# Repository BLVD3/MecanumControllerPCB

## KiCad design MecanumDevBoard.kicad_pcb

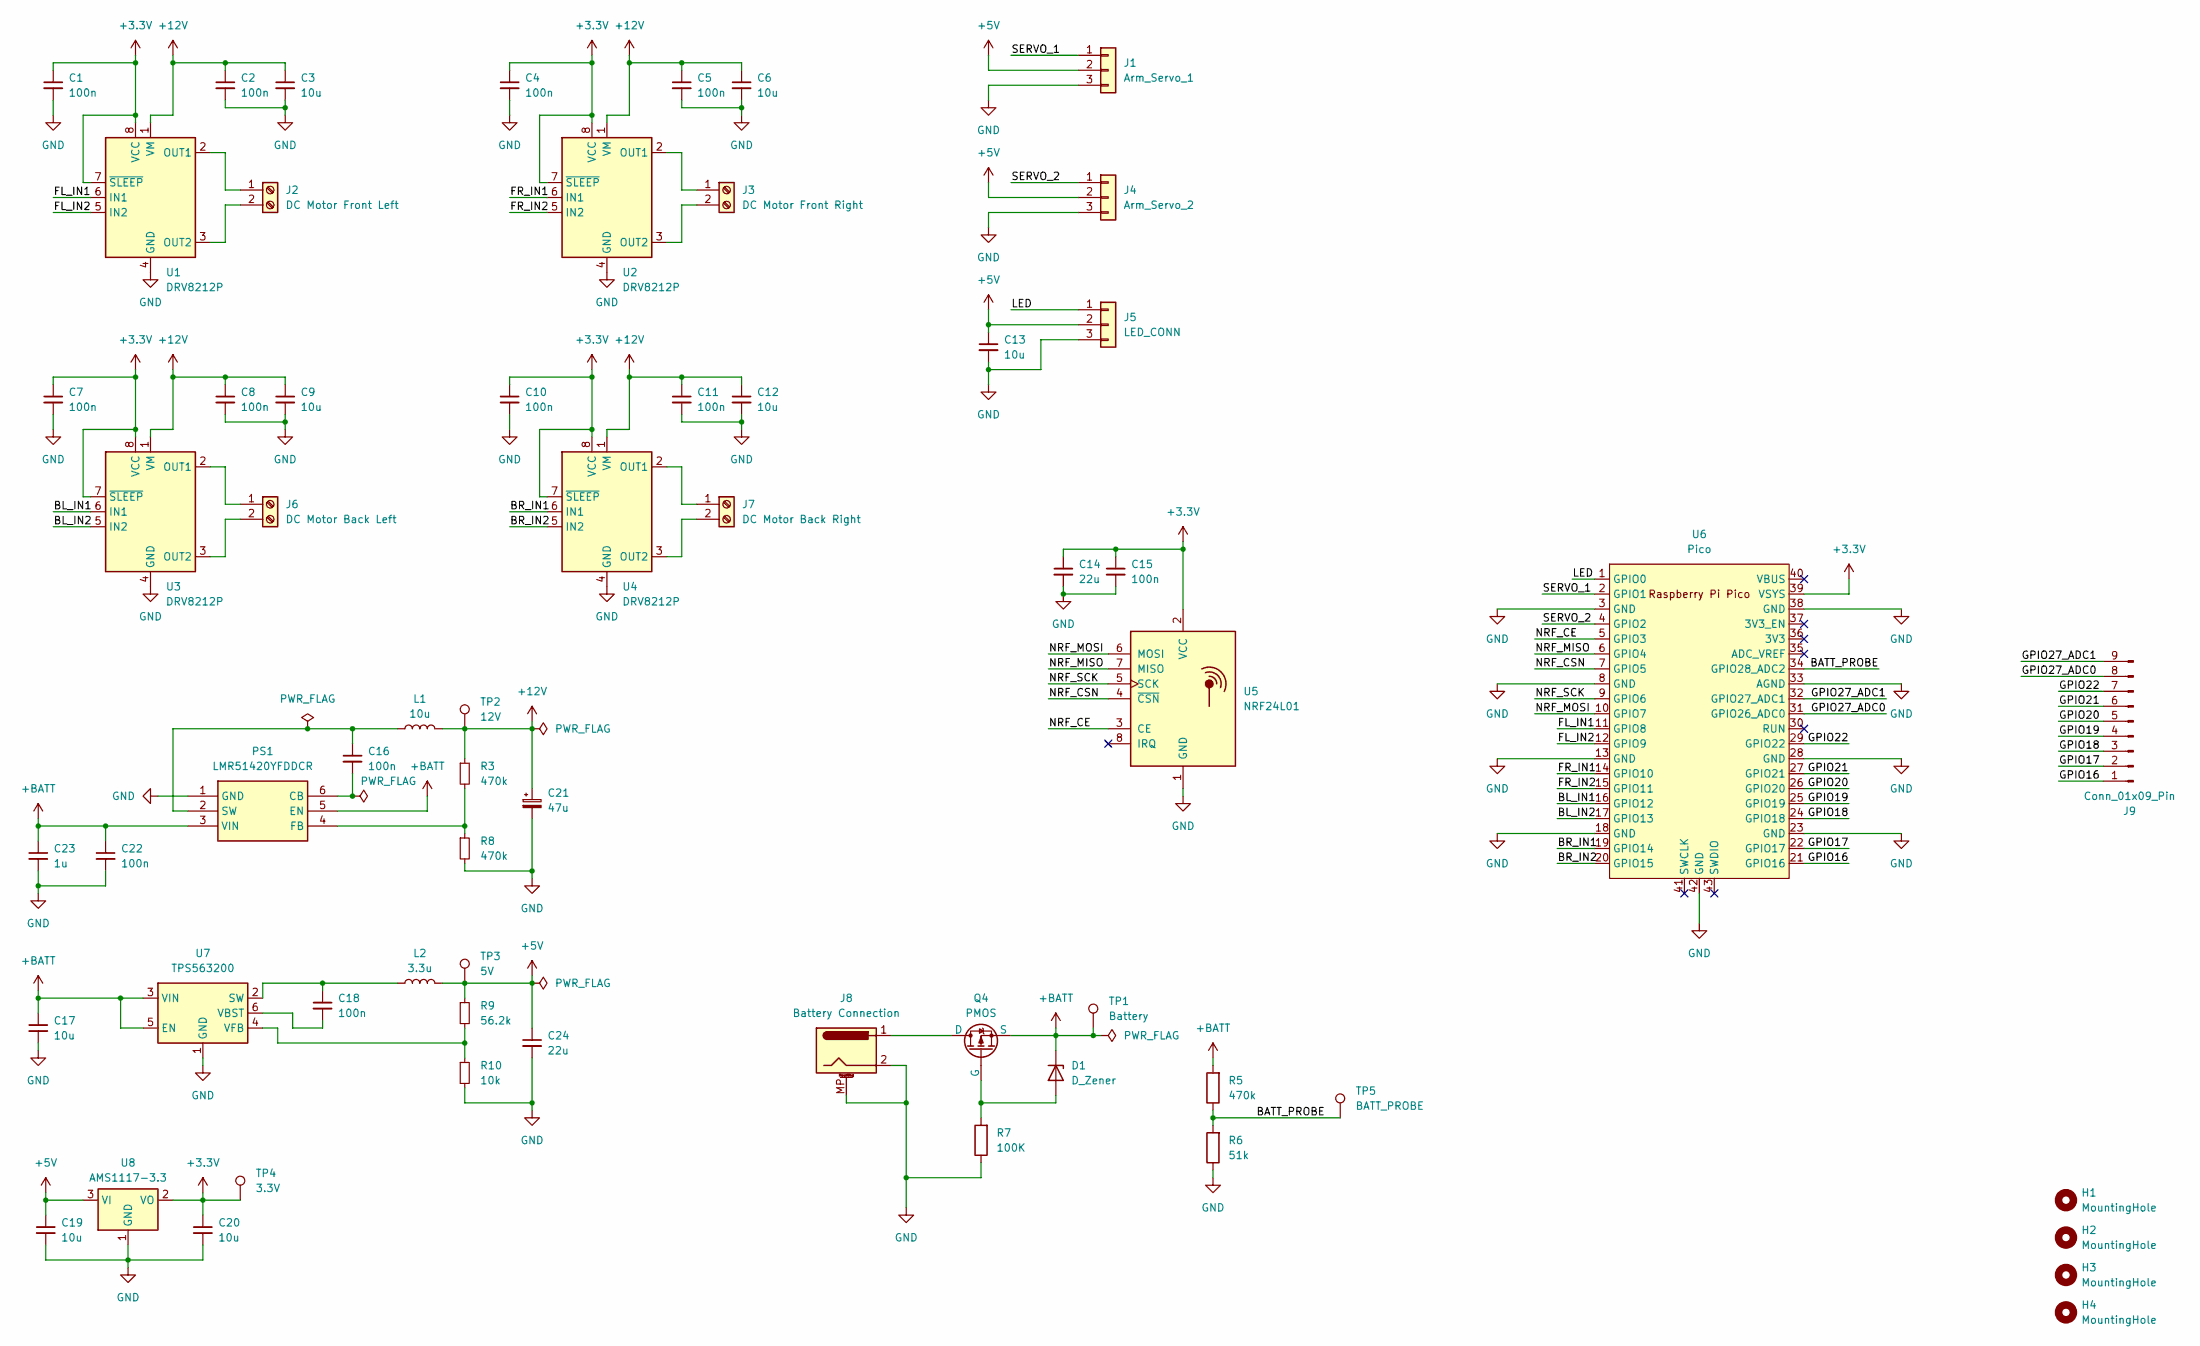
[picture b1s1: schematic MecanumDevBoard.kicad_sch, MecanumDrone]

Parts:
C1, C2, C4, C5, C7, C8, C10, C11, C15, C16, C18, C22: 100n; C_0603_1608Metric
C3, C6, C9, C12, C13, C17, C19, C20: 10u; C_0805_2012Metric
C14, C24: 22u; C_0805_2012Metric
C21: 47u; CP_Radial_D8.0mm_P5.00mm
C23: 1u; C_0603_1608Metric
D1: D_Zener; D_SOD-123
H1, H2, H3, H4: MountingHole; MountingHole_2.2mm_M2
J1: Arm_Servo_1; PinHeader_1x03_P2.54mm_Vertical
J2: DC Motor Front Left; TerminalBlock_Phoenix_MPT-0,5-2-2.54_1x02_P2.54mm_Horizontal
J3: DC Motor Front Right; TerminalBlock_Phoenix_MPT-0,5-2-2.54_1x02_P2.54mm_Horizontal
J4: Arm_Servo_2; PinHeader_1x03_P2.54mm_Vertical
J5: LED_CONN; PinHeader_1x03_P2.54mm_Vertical
J6: DC Motor Back Left; TerminalBlock_Phoenix_MPT-0,5-2-2.54_1x02_P2.54mm_Horizontal
J7: DC Motor Back Right; TerminalBlock_Phoenix_MPT-0,5-2-2.54_1x02_P2.54mm_Horizontal
J8: Battery Connection; BarrelJack_Horizontal
J9: Conn_01x09_Pin; PinHeader_1x09_P2.54mm_Vertical
L1: 10u; L_Bourns-SRN6028
L2: 3.3u; L_Bourns-SRN6028
PS1: LMR51420YFDDCR; SOT95P280X110-6N; Manufacturer_Part_Number LMR51420YFDDCR; Mouser Part Number 595-LMR51420YFDDCR
Q4: PMOS; SOT-23
R3, R5, R8: 470k; R_0805_2012Metric
R6: 51k; R_0603_1608Metric
R7: 100K; R_0805_2012Metric
R9: 56.2k; R_0603_1608Metric
R10: 10k; R_0805_2012Metric
TP1: Battery; TestPoint_Pad_D1.0mm
TP2: 12V; TestPoint_Pad_D1.0mm
TP3: 5V; TestPoint_Pad_D1.0mm
TP4: 3.3V; TestPoint_Pad_D1.0mm
TP5: BATT_PROBE; TestPoint_Pad_D1.0mm
U1, U2, U3, U4: DRV8212P; WSON-8-1EP_2x2mm_P0.5mm_EP0.9x1.6mm
U5: NRF24L01; nRF24L01_Breakout
U6: Pico; RPi_Pico_SMD_TH
U7: TPS563200; SOT-23-6
U8: AMS1117-3.3; SOT-223-3_TabPin2

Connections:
+3.3V: C1.1, C4.1, C7.1, C10.1, C14.1, C15.1, C20.1, TP4.1, U1.7 (~SLEEP), U1.8 (VCC), U2.7 (~SLEEP), U2.8 (VCC), U3.7 (~SLEEP), U3.8 (VCC), U4.7 (~SLEEP), U4.8 (VCC), U5.2 (VCC), U6.39 (VSYS), U8.2 (VO)
+5V: C13.1, C19.1, C24.1, J1.2, J4.2, J5.2, L2.2, R9.1, TP3.1, U8.3 (VI)
+12V: C2.1, C3.1, C5.1, C6.1, C8.1, C9.1, C11.1, C12.1, C21.1, L1.2, R3.1, TP2.1, U1.1 (VM), U2.1 (VM), U3.1 (VM), U4.1 (VM)
+BATT: C17.1, C22.1, C23.1, D1.1 (K), PS1.3 (VIN), PS1.5 (EN), Q4.3 (S), R5.2, TP1.1, U7.3 (VIN), U7.5 (EN)
/BATT_PROBE: R5.1, R6.2, TP5.1, U6.34 (GPIO28_ADC2)
/BL_IN1: U3.6 (IN1), U6.16 (GPIO12)
/BL_IN2: U3.5 (IN2), U6.17 (GPIO13)
/BR_IN1: U4.6 (IN1), U6.19 (GPIO14)
/BR_IN2: U4.5 (IN2), U6.20 (GPIO15)
/FL_IN1: U1.6 (IN1), U6.11 (GPIO8)
/FL_IN2: U1.5 (IN2), U6.12 (GPIO9)
/FR_IN1: U2.6 (IN1), U6.14 (GPIO10)
/FR_IN2: U2.5 (IN2), U6.15 (GPIO11)
/GPIO16: J9.1, U6.21 (GPIO16)
/GPIO17: J9.2, U6.22 (GPIO17)
/GPIO18: J9.3, U6.24 (GPIO18)
/GPIO19: J9.4, U6.25 (GPIO19)
/GPIO20: J9.5, U6.26 (GPIO20)
/GPIO21: J9.6, U6.27 (GPIO21)
/GPIO22: J9.7, U6.29 (GPIO22)
/GPIO27_ADC0: J9.8, U6.31 (GPIO26_ADC0)
/GPIO27_ADC1: J9.9, U6.32 (GPIO27_ADC1)
/LED: J5.1, U6.1 (GPIO0)
/NRF_CE: U5.3 (CE), U6.5 (GPIO3)
/NRF_CSN: U5.4 (~CSN), U6.7 (GPIO5)
/NRF_MISO: U5.7 (MISO), U6.6 (GPIO4)
/NRF_MOSI: U5.6 (MOSI), U6.10 (GPIO7)
/NRF_SCK: U5.5 (SCK), U6.9 (GPIO6)
/SERVO_1: J1.1, U6.2 (GPIO1)
/SERVO_2: J4.1, U6.4 (GPIO2)
GND: C1.2, C2.2, C3.2, C4.2, C5.2, C6.2, C7.2, C8.2, C9.2, C10.2, C11.2, C12.2, C13.2, C14.2, C15.2, C17.2, C19.2, C20.2, C21.2, C22.2, C23.2, C24.2, J1.3, J4.3, J5.3, J8.2, J8.MP (MountPin), PS1.1 (GND), R6.1, R7.1, R8.2, R10.2, U1.4 (GND), U1.9 (GND), U2.4 (GND), U2.9 (GND), U3.4 (GND), U3.9 (GND), U4.4 (GND), U4.9 (GND), U5.1 (GND), U6.3 (GND), U6.8 (GND), U6.13 (GND), U6.18 (GND), U6.23 (GND), U6.28 (GND), U6.33 (AGND), U6.38 (GND), U6.42 (GND), U7.1 (GND), U8.1 (GND)
unnamed: D1.2 (A), Q4.2 (G), R7.2
unnamed: J2.1, U1.2 (OUT1)
unnamed: J2.2, U1.3 (OUT2)
unnamed: J3.1, U2.2 (OUT1)
unnamed: J3.2, U2.3 (OUT2)
unnamed: J6.1, U3.2 (OUT1)
unnamed: J6.2, U3.3 (OUT2)
unnamed: J7.1, U4.2 (OUT1)
unnamed: J7.2, U4.3 (OUT2)
unnamed: C16.2, PS1.6 (CB)
unnamed: PS1.4 (FB), R3.2, R8.1
unnamed: C16.1, L1.1, PS1.2 (SW)
unnamed: J8.1, Q4.1 (D)
unnamed: C18.1, L2.1, U7.2 (SW)
unnamed: C18.2, U7.6 (VBST)
unnamed: R9.2, R10.1, U7.4 (VFB)

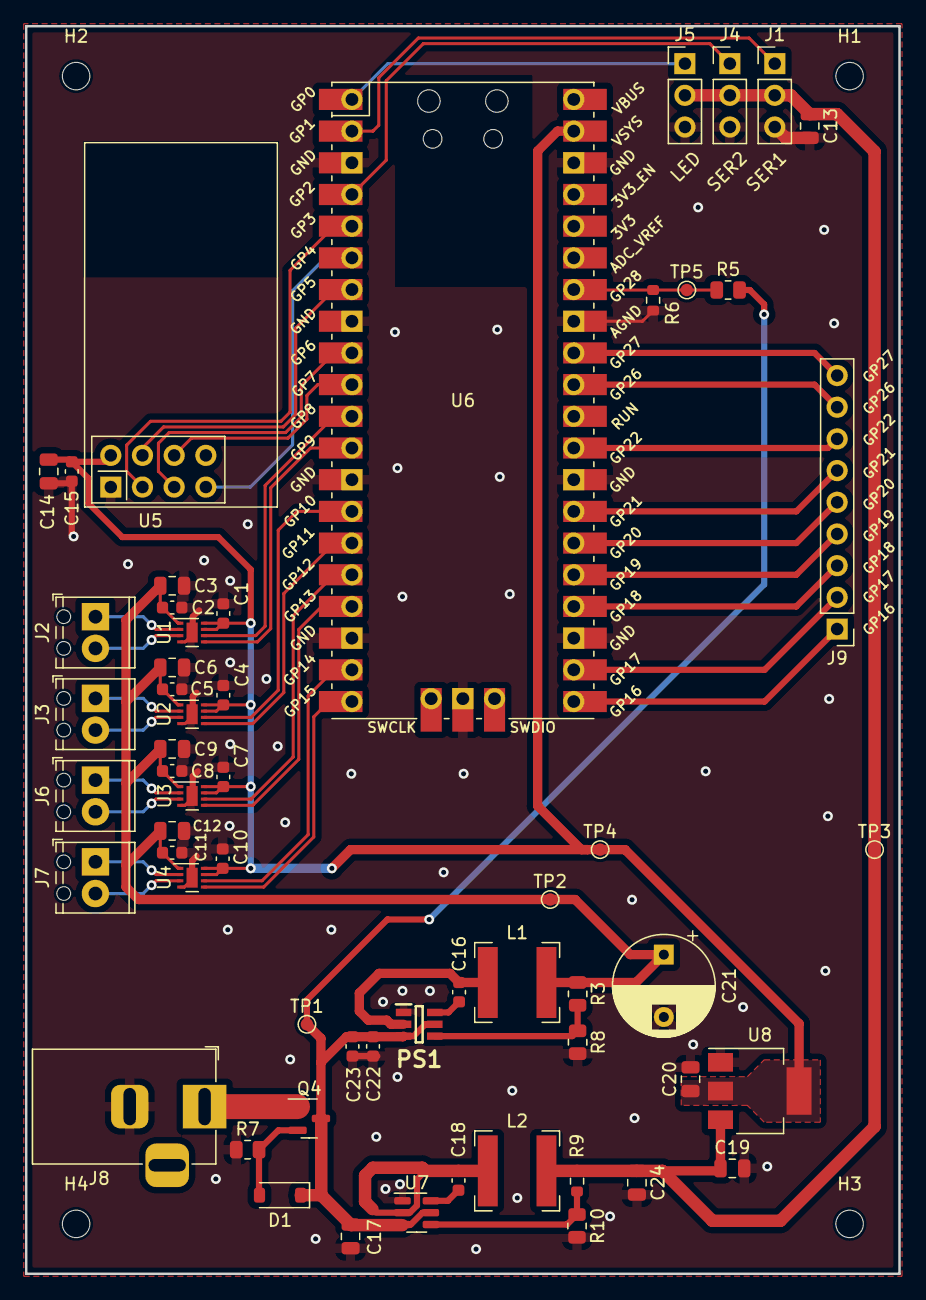
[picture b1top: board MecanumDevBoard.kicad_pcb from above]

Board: 2 copper layers, 70.0 x 100.0 mm, 62 parts (0 on the bottom side), 47 nets.

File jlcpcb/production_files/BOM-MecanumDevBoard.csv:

Comment,Designator,Footprint,LCSC
100n,"C1,C10,C11,C15,C16,C18,C2,C22,C4,C5,C7,C8",C_0603_1608Metric,C14663
100K,R7,R_0805_2012Metric,C149504
PMOS,Q4,SOT-23,C15127
1u,C23,C_0603_1608Metric,C15849
10u,"C12,C13,C17,C19,C20,C3,C6,C9",C_0805_2012Metric,C15850
10k,R10,R_0805_2012Metric,C17414
470k,"R3,R5,R8",R_0805_2012Metric,C17709
51k,R6,R_0603_1608Metric,C23196
56.2k,R9,R_0603_1608Metric,C23206
DRV8212P,"U1,U2,U3,U4",WSON-8-1EP_2x2mm_P0.5mm_EP0.9x1.6mm,C2843766
22u,"C14,C24",C_0805_2012Metric,C45783
LMR51420YFDDCR,PS1,SOT95P280X110-6N,C5383002
AMS1117-3.3,U8,SOT-223-3_TabPin2,C6186
TPS563200,U7,SOT-23-6,C97253

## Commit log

2023-12-19 Updated Production Files
